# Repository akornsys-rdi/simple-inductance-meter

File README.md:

# Simple Inductance Meter

My implementation of the simple inductance meter designed by Danyk [(http://www.danyk.cz/lmetr_en.html)](http://www.danyk.cz/lmetr_en.html).

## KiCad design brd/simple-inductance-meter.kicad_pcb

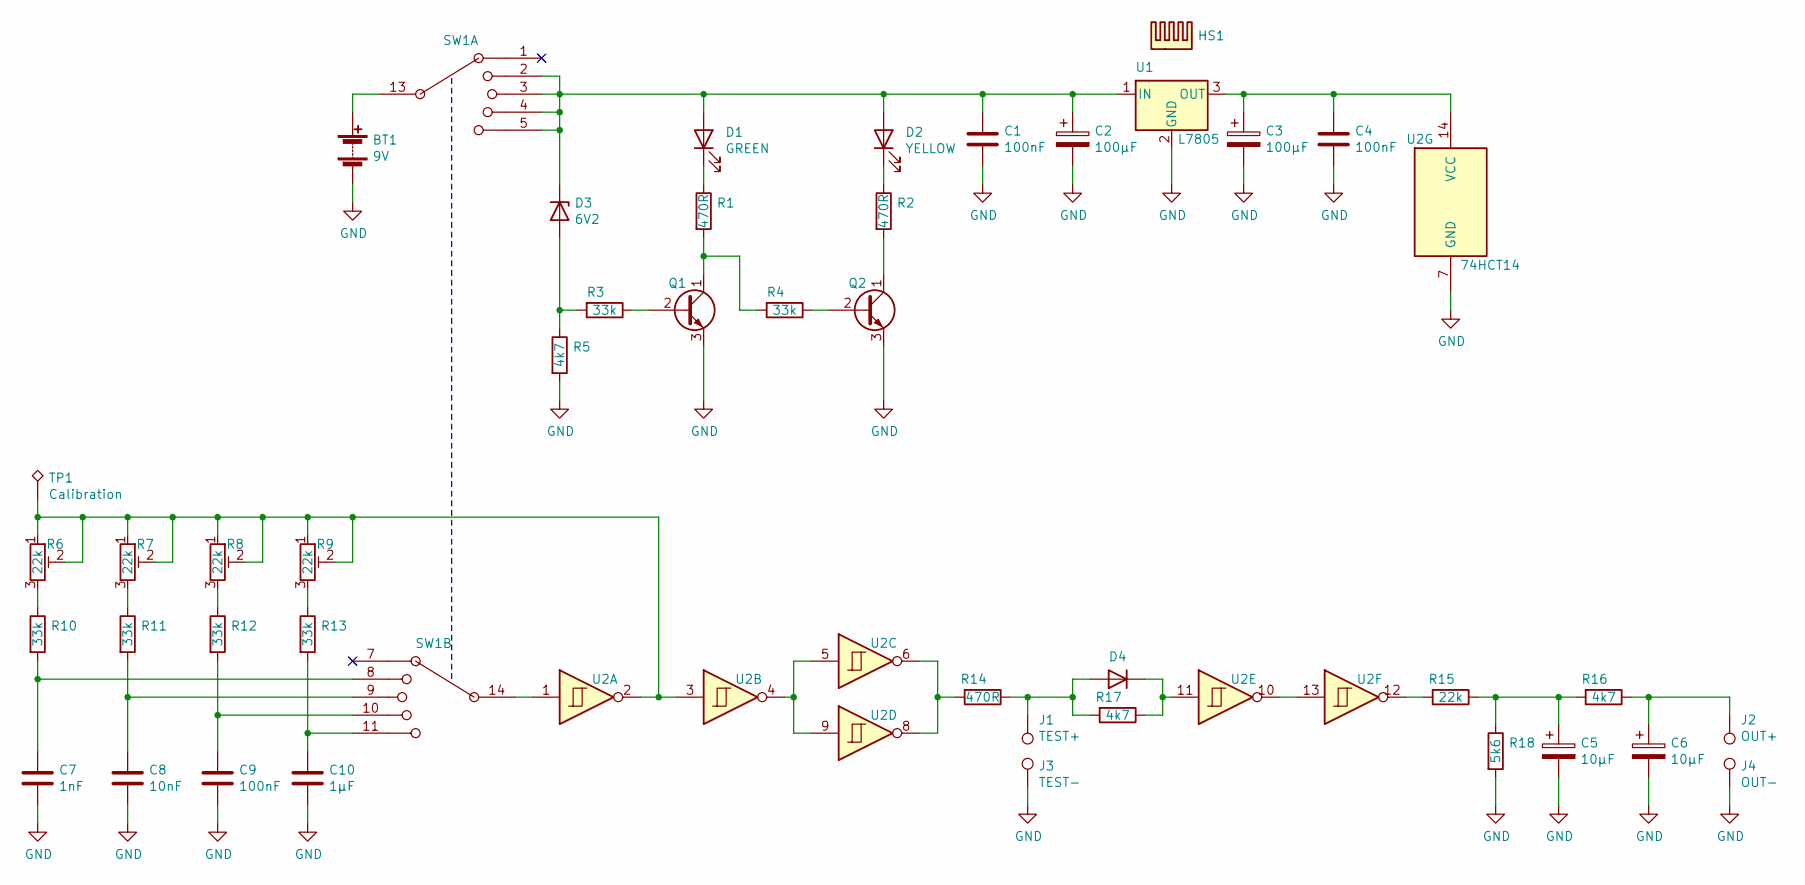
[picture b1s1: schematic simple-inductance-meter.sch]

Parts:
BT1: 9V; SolderWire-0.5sqmm_1x02_P4.6mm_D0.9mm_OD2.1mm; Manufacturer Part Number 233
C1, C4, C9: 100nF; C_Disc_D4.7mm_W2.5mm_P5.00mm; Manufacturer Part Number K104K15X7RF53H5
C2, C3: 100µF; CP_Radial_D6.3mm_P2.50mm; Manufacturer Part Number 860010473007
C5, C6: 10µF; CP_Radial_Tantal_D5.0mm_P5.00mm; Manufacturer Part Number TAP106K016CRW
C7: 1nF; C_Disc_D4.7mm_W2.5mm_P5.00mm; Manufacturer Part Number K102K15X7RH5UH5
C8: 10nF; C_Disc_D4.7mm_W2.5mm_P5.00mm; Manufacturer Part Number 1C20X7R103K100B
C10: 1µF; C_Disc_D4.7mm_W2.5mm_P5.00mm; Manufacturer Part Number FG28X5R1H105KRT00
D1: GREEN; LED_D5.0mm; Manufacturer Part Number LTL-4233
D2: YELLOW; LED_D5.0mm; Manufacturer Part Number LTL-4273
D3: 6V2; D_DO-41_SOD81_P10.16mm_Horizontal; Manufacturer Part Number BZX85C6V2-TAP
D4: 1N4148; D_DO-35_SOD27_P7.62mm_Horizontal; Manufacturer Part Number 1N4148TR
HS1: TO220 Heatsink; Heatsink_Aavid-TV5G_TO220_Horizontal; Manufacturer Part Number 577002B00000G
J1: TEST+; Banana_Jack_1Pin; Manufacturer Part Number 164-R109R-EX
J2: OUT+; Banana_Jack_1Pin; Manufacturer Part Number 164-R109R-EX
J3: TEST-; Banana_Jack_1Pin; Manufacturer Part Number 164-R109B-EX
J4: OUT-; Banana_Jack_1Pin; Manufacturer Part Number 164-R109B-EX
Q1, Q2: BC547; TO-92_Inline_Wide; Manufacturer Part Number BC547BTA
R1, R2, R14: 470R; R_Axial_DIN0204_L3.6mm_D1.6mm_P2.54mm_Vertical; Manufacturer Part Number MF0204FTE52-470R
R3, R4, R10, R11, R12, R13: 33k; R_Axial_DIN0204_L3.6mm_D1.6mm_P2.54mm_Vertical; Manufacturer Part Number MF0204FTE52-33K
R5, R16, R17: 4k7; R_Axial_DIN0204_L3.6mm_D1.6mm_P2.54mm_Vertical; Manufacturer Part Number MFR25SFRF52-4K7
R6, R7, R8, R9: 22k; Potentiometer_Bourns_3296Y_Vertical; Manufacturer Part Number 3296Y-1-223LF
R15: 22k; R_Axial_DIN0204_L3.6mm_D1.6mm_P2.54mm_Vertical; Manufacturer Part Number MFR-25FTE52-22K
R18: 5k6; R_Axial_DIN0204_L3.6mm_D1.6mm_P2.54mm_Vertical; Manufacturer Part Number MFR-25FTE52-5K6
SW1: SW_Rotary2x5; Manufacturer Part Number SR2511F-0205-19F0B-E9-N-W-159
TP1: Calibration; TestPoint_Loop_D2.50mm_Drill1.0mm
U1: L7805; TO-220-3_Horizontal_TabDown; Manufacturer Part Number L7805ABV
U2: 74HCT14; DIP-14_W7.62mm_LongPads; Manufacturer Part Number SN74HCT14N

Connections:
GND: BT1.2 (-), C1.2, C2.2, C3.2, C4.2, C5.2, C6.2, C7.2, C8.2, C9.2, C10.2, J3.1, J4.1, Q1.3 (E), Q2.3 (E), R5.2, R18.2, U1.2 (GND), U2.7 (GND)
unnamed: BT1.1 (+), SW1.13 (14)
unnamed: C1.1, C2.1, D1.2 (A), D2.2 (A), D3.1 (K), SW1.2, SW1.3, SW1.4, SW1.5, U1.1 (IN)
unnamed: C3.1, C4.1, U1.3 (OUT), U2.14 (VCC)
unnamed: C5.1, R15.1, R16.2, R18.1
unnamed: C6.1, J2.1, R16.1
unnamed: C7.1, R10.2, SW1.8 (2)
unnamed: C8.1, R11.2, SW1.9 (3)
unnamed: C9.1, R12.2, SW1.10 (4)
unnamed: C10.1, R13.2, SW1.11 (5)
unnamed: D1.1 (K), R1.1
unnamed: D2.1 (K), R2.1
unnamed: D3.2 (A), R3.2, R5.1
unnamed: D4.1 (K), R17.1, U2.11
unnamed: D4.2 (A), J1.1, R14.1, R17.2
unnamed: Q1.1 (C), R1.2, R4.2
unnamed: Q1.2 (B), R3.1
unnamed: Q2.1 (C), R2.2
unnamed: Q2.2 (B), R4.1
unnamed: R6.1, R6.2, R7.1, R7.2, R8.1, R8.2, R9.1, R9.2, TP1.1, U2.2, U2.3
unnamed: R6.3, R10.1
unnamed: R7.3, R11.1
unnamed: R8.3, R12.1
unnamed: R9.3, R13.1
unnamed: R14.2, U2.6, U2.8
unnamed: R15.2, U2.12
unnamed: SW1.14, U2.1
unnamed: U2.4, U2.5, U2.9
unnamed: U2.10, U2.13

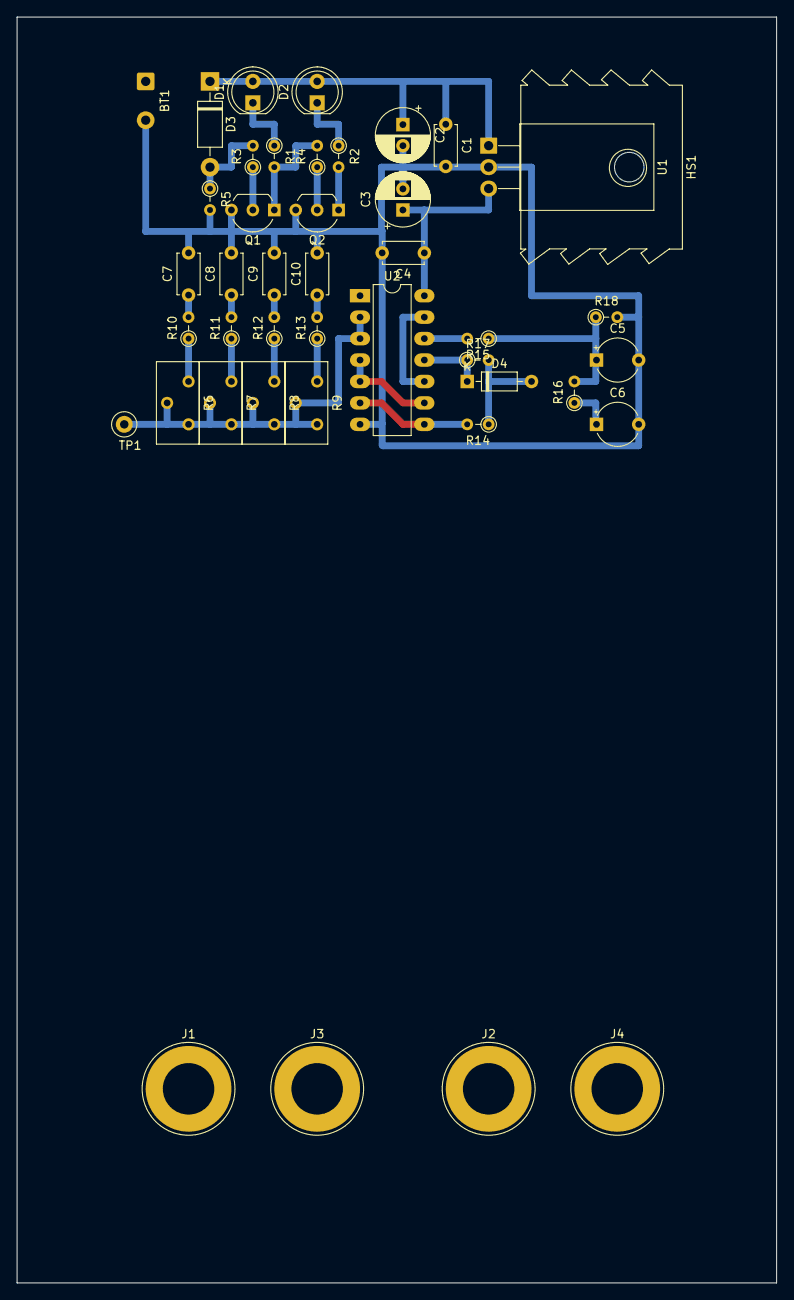
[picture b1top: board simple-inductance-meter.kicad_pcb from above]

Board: 2 copper layers, 90.0 x 150.0 mm, 43 parts (0 on the bottom side), 27 nets.

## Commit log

2021-05-23 upload project
